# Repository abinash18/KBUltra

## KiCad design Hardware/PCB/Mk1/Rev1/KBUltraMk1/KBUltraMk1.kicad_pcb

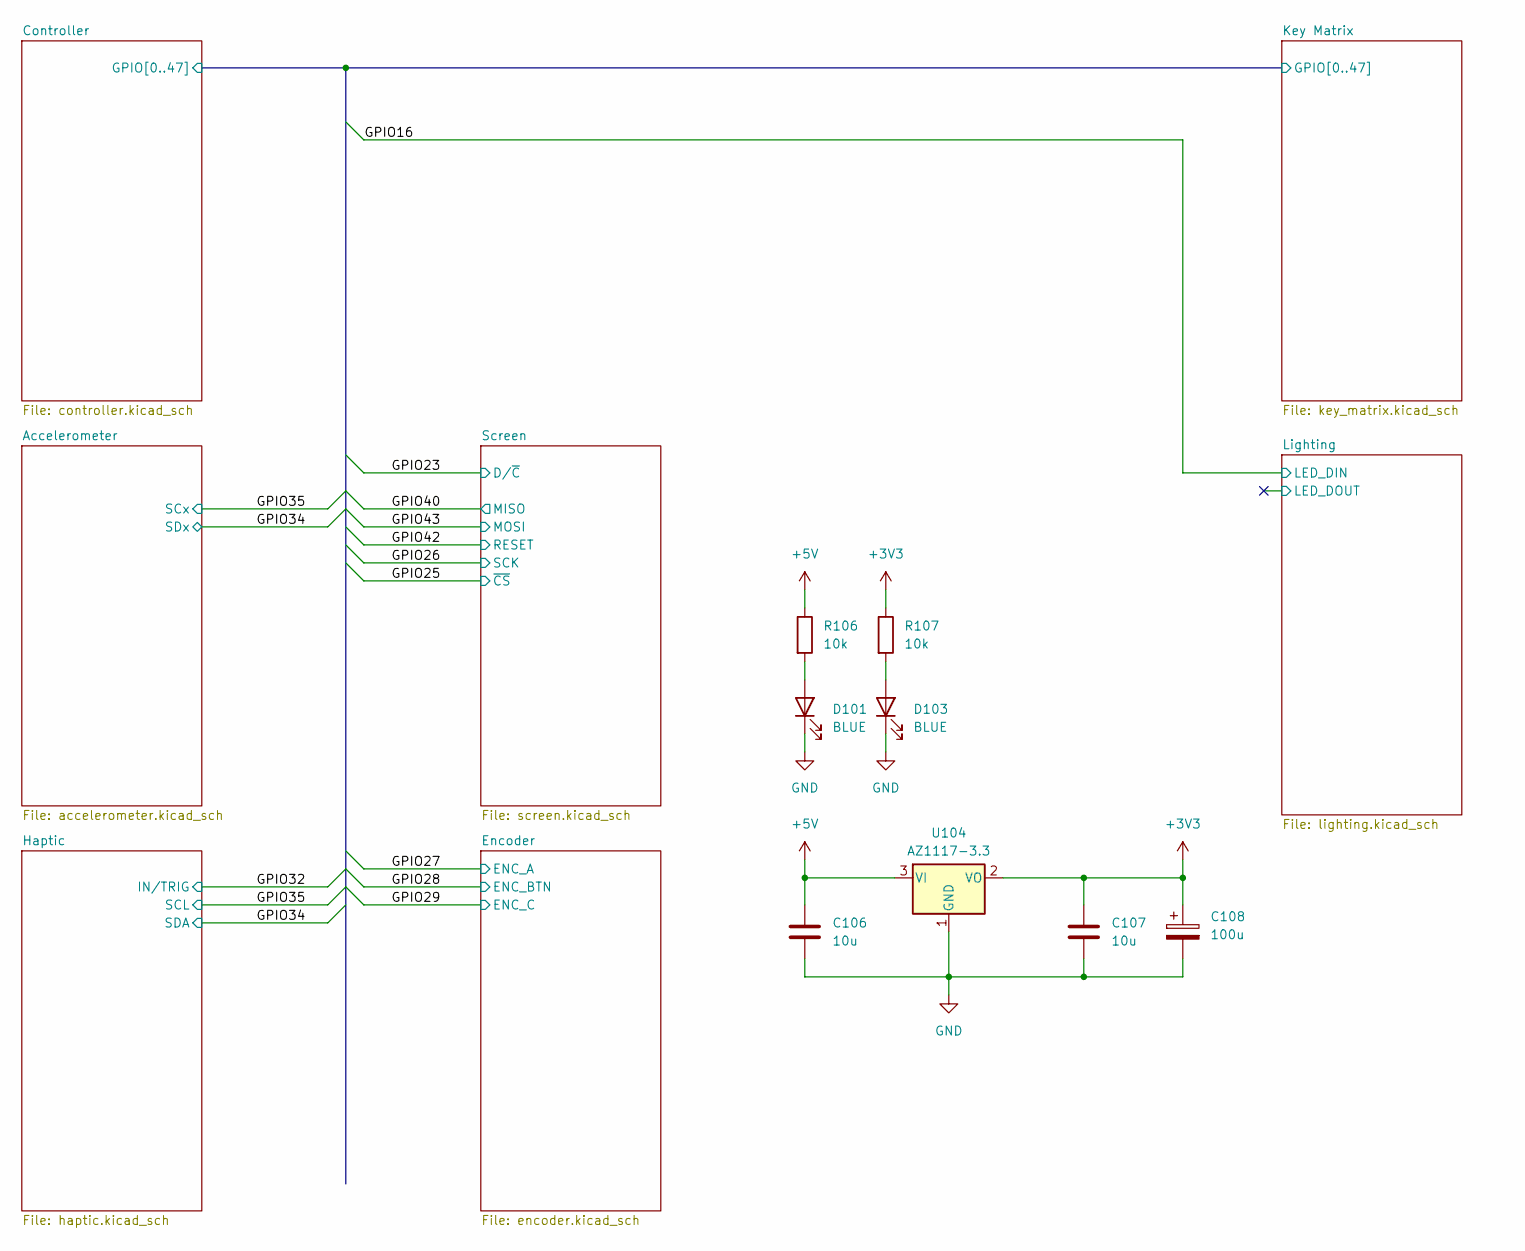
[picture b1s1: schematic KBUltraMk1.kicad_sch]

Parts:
C106, C107: 10u; C_0603_1608Metric; JLC Part# C96446
C108: 100u; CP_EIA-3528-21_Kemet-B_HandSolder; JLC Part# C16133
D101, D103: BLUE; LED_0603_1608Metric
R106, R107: 10k; R_0603_1608Metric; JLC Part# C25804
U104: AZ1117-3.3; SOT-223-3_TabPin2

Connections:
+3V3: C107.2, C108.1, R107.1, U104.2 (VO); also elsewhere on the board
+5V: C106.2, R106.1, U104.3 (VI); also elsewhere on the board
GND: C106.1, C107.1, C108.2, D101.1 (K), D103.1 (K), U104.1 (GND); also elsewhere on the board
unnamed: D101.2 (A), R106.2
unnamed: D103.2 (A), R107.2

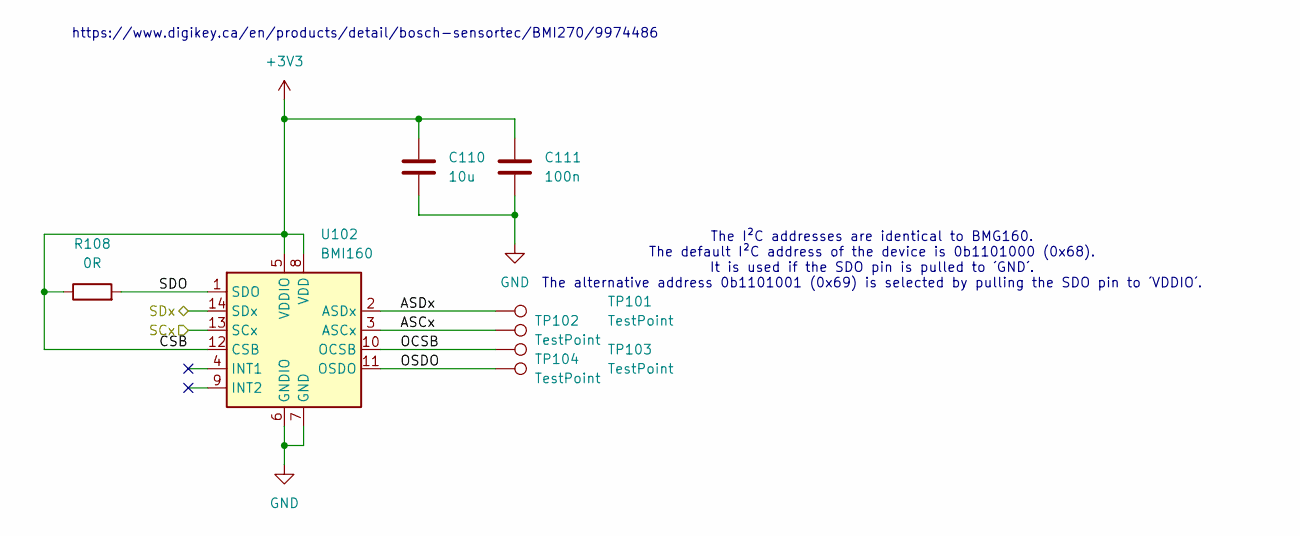
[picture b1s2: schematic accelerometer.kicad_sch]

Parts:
C110: 10u; C_0603_1608Metric; JLC Part# C96446
C111: 100n; C_0603_1608Metric; JLC Part# C14663
R108: 0R; R_0603_1608Metric; JLC Part# C21189
TP101, TP102, TP103, TP104: TestPoint; TestPoint_Pad_D1.0mm
U102: BMI160; Bosch_LGA-14_3x2.5mm_P0.5mm

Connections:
+3V3: C110.1, C111.1, R108.1, U102.5 (VDDIO), U102.8 (VDD), U102.12 (CSB); also elsewhere on the board
/Accelerometer/ASCx: TP102.1 (1_1), U102.3 (ASCx)
/Accelerometer/ASDx: TP101.1 (1_1), U102.2 (ASDx)
/Accelerometer/OCSB: TP103.1 (1_1), U102.10 (OCSB)
/Accelerometer/OSDO: TP104.1 (1_1), U102.11 (OSDO)
/Accelerometer/SDO: R108.2, U102.1 (SDO)
/Controller/GPIO34: U102.14 (SDx); also elsewhere on the board
/Controller/GPIO35: U102.13 (SCx); also elsewhere on the board
GND: C110.2, C111.2, U102.6 (GNDIO), U102.7 (GND); also elsewhere on the board

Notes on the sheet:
The I²C addresses are identical to BMG160. The default I²C address of the device is 0b1101000 (0x68). It is used if the SDO pin is pulled to ´GND´. The alternative address 0b1101001 (0x69) is selected by pulling the SDO pin to ´VDDIO´.
https://www.digikey.ca/en/products/detail/bosch-sensortec/BMI270/9974486

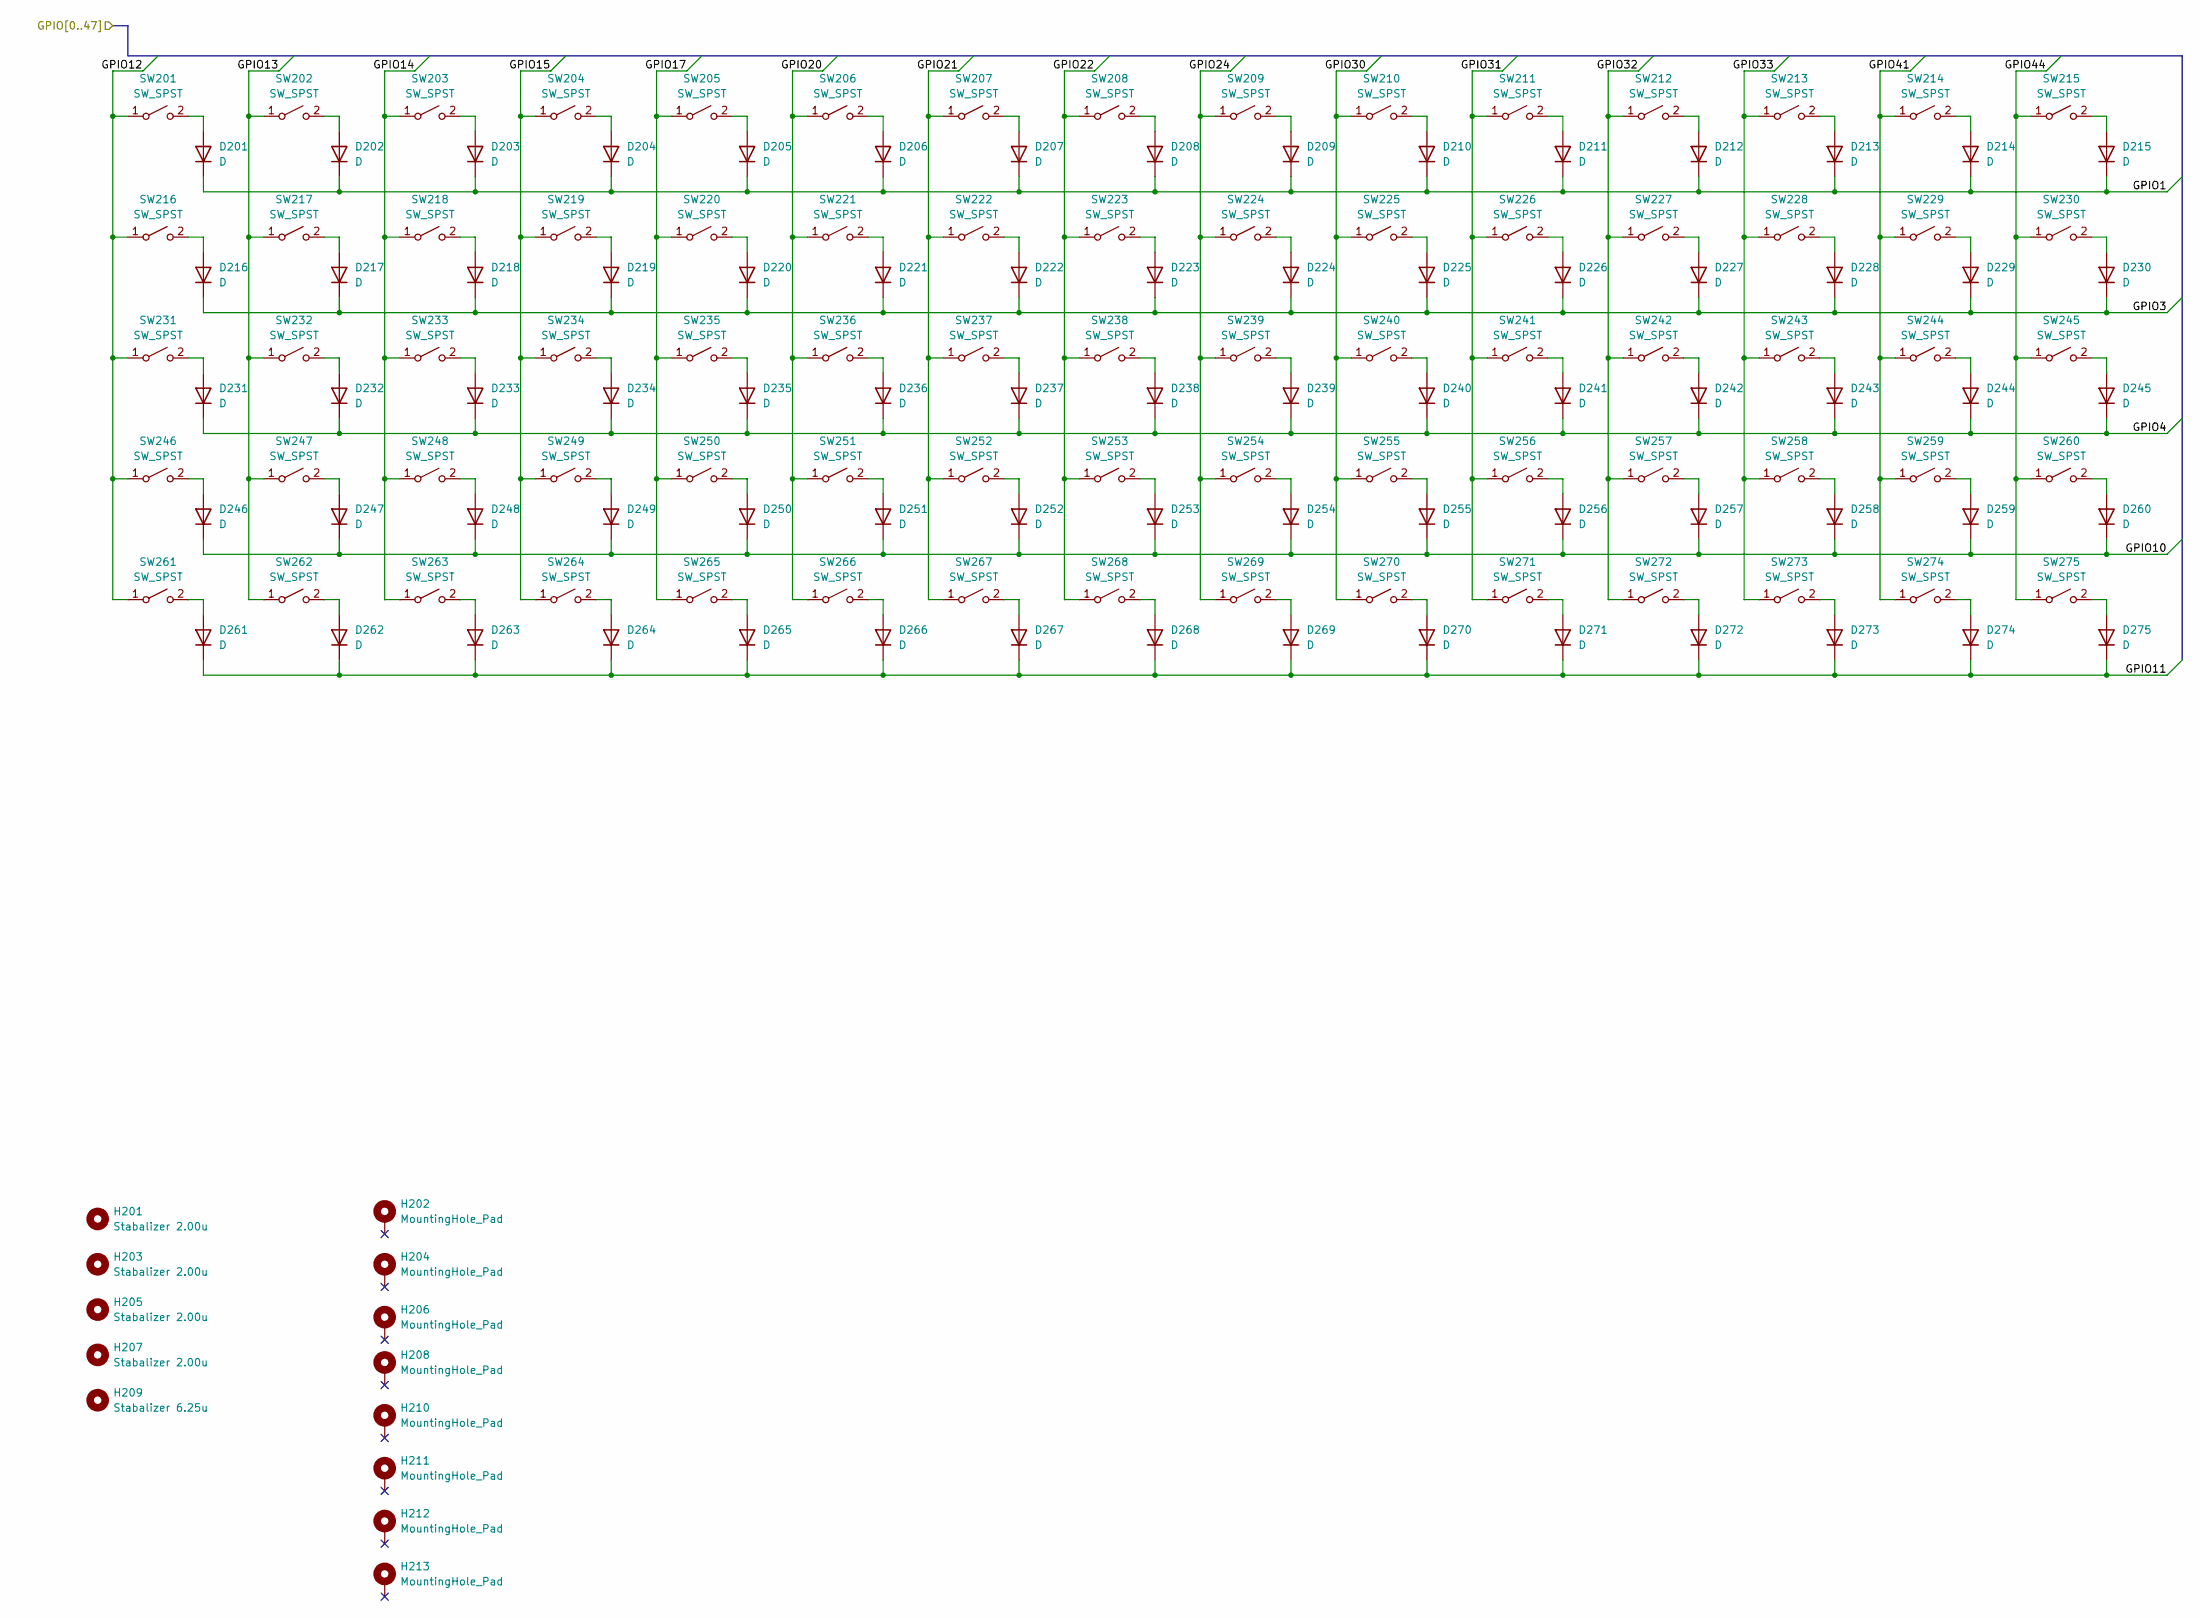
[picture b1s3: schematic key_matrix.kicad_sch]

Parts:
D201, D202, D203, D204, D205, D206, D207, D208, D209, D210, D211, D212, D213, D214, D215, D216, D217, D218, D219, D220, D221, D222, D223, D224, D225, D226, D227, D228, D229, D230, D231, D232, D233, D234, D235, D236, D237, D238, D239, D240, D241, D242, D243, D244, D245, D246, D247, D248, D249, D250, D251, D252, D253, D254, D255, D256, D257, D258, D259, D260, D261, D262, D263, D264, D265, D266, D267, D268, D269, D270, D271, D272, D273, D274, D275: D; D_SOD-123; JLC Part# C81598
H201, H203, H205, H207: Stabalizer 2.00u; Stabilizer_Cherry_MX_2.00u
H202, H204, H206, H208, H210, H211, H212, H213: MountingHole_Pad; MountingHole_3.2mm_M3_Pad_Via
H209: Stabalizer 6.25u; Stabilizer_Cherry_MX_6.25u
SW201, SW202, SW203, SW204, SW205, SW206, SW207, SW208, SW209, SW210, SW211, SW212, SW213, SW214, SW215, SW216, SW217, SW218, SW219, SW220, SW221, SW222, SW223, SW224, SW226, SW228, SW229, SW230, SW231, SW232, SW233, SW234, SW235, SW236, SW237, SW238, SW239, SW241, SW243, SW244, SW245, SW246, SW247, SW248, SW249, SW250, SW251, SW252, SW253, SW255, SW257, SW258, SW259, SW260, SW261, SW262, SW263, SW264, SW265, SW266: SW_SPST; SW_Hotswap_Kailh_MX_Plated_1.00u; JLC Part# C41430893
SW225: SW_SPST; SW_Hotswap_Kailh_MX_Plated_2.00u; JLC Part# C41430893
SW227, SW240: SW_SPST; SW_Hotswap_Kailh_MX_Plated_1.50u; JLC Part# C41430893
SW242: SW_SPST; SW_Hotswap_Kailh_MX_Plated_1.75u; JLC Part# C41430893
SW254, SW256: SW_SPST; SW_Hotswap_Kailh_MX_Plated_2.25u; JLC Part# C41430893
SW267: SW_SPST; SW_Hotswap_Kailh_MX_Plated_2.75u; JLC Part# C41430893
SW268, SW269, SW270, SW272, SW273, SW274, SW275: SW_SPST; SW_Hotswap_Kailh_MX_Plated_1.25u; JLC Part# C41430893
SW271: SW_SPST; SW_Hotswap_Kailh_MX_Plated_6.25u; JLC Part# C41430893

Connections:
/Controller/GPIO1: D201.1 (K), D202.1 (K), D203.1 (K), D204.1 (K), D205.1 (K), D206.1 (K), D207.1 (K), D208.1 (K), D209.1 (K), D210.1 (K), D211.1 (K), D212.1 (K), D213.1 (K), D214.1 (K), D215.1 (K); also elsewhere on the board
/Controller/GPIO3: D216.1 (K), D217.1 (K), D218.1 (K), D219.1 (K), D220.1 (K), D221.1 (K), D222.1 (K), D223.1 (K), D224.1 (K), D225.1 (K), D226.1 (K), D227.1 (K), D228.1 (K), D229.1 (K), D230.1 (K); also elsewhere on the board
/Controller/GPIO4: D231.1 (K), D232.1 (K), D233.1 (K), D234.1 (K), D235.1 (K), D236.1 (K), D237.1 (K), D238.1 (K), D239.1 (K), D240.1 (K), D241.1 (K), D242.1 (K), D243.1 (K), D244.1 (K), D245.1 (K); also elsewhere on the board
/Controller/GPIO10: D246.1 (K), D247.1 (K), D248.1 (K), D249.1 (K), D250.1 (K), D251.1 (K), D252.1 (K), D253.1 (K), D254.1 (K), D255.1 (K), D256.1 (K), D257.1 (K), D258.1 (K), D259.1 (K), D260.1 (K); also elsewhere on the board
/Controller/GPIO11: D261.1 (K), D262.1 (K), D263.1 (K), D264.1 (K), D265.1 (K), D266.1 (K), D267.1 (K), D268.1 (K), D269.1 (K), D270.1 (K), D271.1 (K), D272.1 (K), D273.1 (K), D274.1 (K), D275.1 (K); also elsewhere on the board
/Controller/GPIO12: SW201.1 (A), SW216.1 (A), SW231.1 (A), SW246.1 (A), SW261.1 (A); also elsewhere on the board
/Controller/GPIO13: SW202.1 (A), SW217.1 (A), SW232.1 (A), SW247.1 (A), SW262.1 (A); also elsewhere on the board
/Controller/GPIO14: SW203.1 (A), SW218.1 (A), SW233.1 (A), SW248.1 (A), SW263.1 (A); also elsewhere on the board
/Controller/GPIO15: SW204.1 (A), SW219.1 (A), SW234.1 (A), SW249.1 (A), SW264.1 (A); also elsewhere on the board
/Controller/GPIO17: SW205.1 (A), SW220.1 (A), SW235.1 (A), SW250.1 (A), SW265.1 (A); also elsewhere on the board
/Controller/GPIO20: SW206.1 (A), SW221.1 (A), SW236.1 (A), SW251.1 (A), SW266.1 (A); also elsewhere on the board
/Controller/GPIO21: SW207.1 (A), SW222.1 (A), SW237.1 (A), SW252.1 (A), SW267.1 (A); also elsewhere on the board
/Controller/GPIO22: SW208.1 (A), SW223.1 (A), SW238.1 (A), SW253.1 (A), SW268.1 (A); also elsewhere on the board
/Controller/GPIO24: SW209.1 (A), SW224.1 (A), SW239.1 (A), SW254.1 (A), SW269.1 (A); also elsewhere on the board
/Controller/GPIO30: SW210.1 (A), SW225.1 (A), SW240.1 (A), SW255.1 (A), SW270.1 (A); also elsewhere on the board
/Controller/GPIO31: SW211.1 (A), SW226.1 (A), SW241.1 (A), SW256.1 (A), SW271.1 (A); also elsewhere on the board
/Controller/GPIO32: SW212.1 (A), SW227.1 (A), SW242.1 (A), SW257.1 (A), SW272.1 (A); also elsewhere on the board
/Controller/GPIO33: SW213.1 (A), SW228.1 (A), SW243.1 (A), SW258.1 (A), SW273.1 (A); also elsewhere on the board
/Controller/GPIO41: SW214.1 (A), SW229.1 (A), SW244.1 (A), SW259.1 (A), SW274.1 (A); also elsewhere on the board
/Controller/GPIO44: SW215.1 (A), SW230.1 (A), SW245.1 (A), SW260.1 (A), SW275.1 (A); also elsewhere on the board
unnamed: D201.2 (A), SW201.2 (B)
unnamed: D202.2 (A), SW202.2 (B)
unnamed: D203.2 (A), SW203.2 (B)
unnamed: D204.2 (A), SW204.2 (B)
unnamed: D205.2 (A), SW205.2 (B)
unnamed: D206.2 (A), SW206.2 (B)
unnamed: D207.2 (A), SW207.2 (B)
unnamed: D208.2 (A), SW208.2 (B)
unnamed: D209.2 (A), SW209.2 (B)
unnamed: D210.2 (A), SW210.2 (B)
unnamed: D211.2 (A), SW211.2 (B)
unnamed: D212.2 (A), SW212.2 (B)
unnamed: D213.2 (A), SW213.2 (B)
unnamed: D214.2 (A), SW214.2 (B)
unnamed: D215.2 (A), SW215.2 (B)
unnamed: D216.2 (A), SW216.2 (B)
unnamed: D217.2 (A), SW217.2 (B)
unnamed: D218.2 (A), SW218.2 (B)
unnamed: D219.2 (A), SW219.2 (B)
unnamed: D220.2 (A), SW220.2 (B)
unnamed: D221.2 (A), SW221.2 (B)
unnamed: D222.2 (A), SW222.2 (B)
unnamed: D223.2 (A), SW223.2 (B)
unnamed: D224.2 (A), SW224.2 (B)
unnamed: D225.2 (A), SW225.2 (B)
unnamed: D226.2 (A), SW226.2 (B)
unnamed: D227.2 (A), SW227.2 (B)
unnamed: D228.2 (A), SW228.2 (B)
unnamed: D229.2 (A), SW229.2 (B)
unnamed: D230.2 (A), SW230.2 (B)
unnamed: D231.2 (A), SW231.2 (B)
unnamed: D232.2 (A), SW232.2 (B)
unnamed: D233.2 (A), SW233.2 (B)
unnamed: D234.2 (A), SW234.2 (B)
unnamed: D235.2 (A), SW235.2 (B)
unnamed: D236.2 (A), SW236.2 (B)
unnamed: D237.2 (A), SW237.2 (B)
unnamed: D238.2 (A), SW238.2 (B)
unnamed: D239.2 (A), SW239.2 (B)
unnamed: D240.2 (A), SW240.2 (B)
unnamed: D241.2 (A), SW241.2 (B)
unnamed: D242.2 (A), SW242.2 (B)
unnamed: D243.2 (A), SW243.2 (B)
unnamed: D244.2 (A), SW244.2 (B)
unnamed: D245.2 (A), SW245.2 (B)
unnamed: D246.2 (A), SW246.2 (B)
unnamed: D247.2 (A), SW247.2 (B)
unnamed: D248.2 (A), SW248.2 (B)
unnamed: D249.2 (A), SW249.2 (B)
unnamed: D250.2 (A), SW250.2 (B)
unnamed: D251.2 (A), SW251.2 (B)
unnamed: D252.2 (A), SW252.2 (B)
unnamed: D253.2 (A), SW253.2 (B)
unnamed: D254.2 (A), SW254.2 (B)
unnamed: D255.2 (A), SW255.2 (B)
unnamed: D256.2 (A), SW256.2 (B)
unnamed: D257.2 (A), SW257.2 (B)
unnamed: D258.2 (A), SW258.2 (B)
unnamed: D259.2 (A), SW259.2 (B)
unnamed: D260.2 (A), SW260.2 (B)
unnamed: D261.2 (A), SW261.2 (B)
unnamed: D262.2 (A), SW262.2 (B)
unnamed: D263.2 (A), SW263.2 (B)
unnamed: D264.2 (A), SW264.2 (B)
unnamed: D265.2 (A), SW265.2 (B)
unnamed: D266.2 (A), SW266.2 (B)
unnamed: D267.2 (A), SW267.2 (B)
unnamed: D268.2 (A), SW268.2 (B)
unnamed: D269.2 (A), SW269.2 (B)
unnamed: D270.2 (A), SW270.2 (B)
unnamed: D271.2 (A), SW271.2 (B)
unnamed: D272.2 (A), SW272.2 (B)
unnamed: D273.2 (A), SW273.2 (B)
unnamed: D274.2 (A), SW274.2 (B)
unnamed: D275.2 (A), SW275.2 (B)

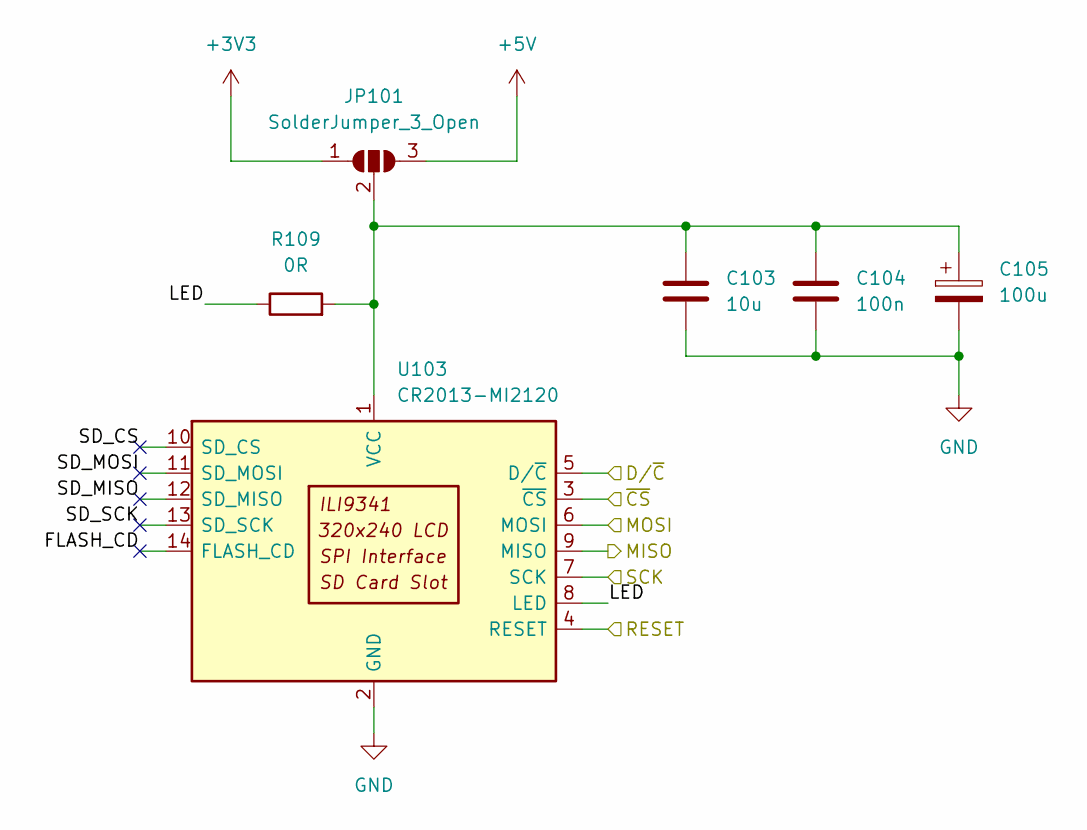
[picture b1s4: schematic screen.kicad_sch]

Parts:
C103: 10u; C_0603_1608Metric; JLC Part# C96446
C104: 100n; C_0603_1608Metric; JLC Part# C14663
C105: 100u; CP_EIA-3528-21_Kemet-B_HandSolder; JLC Part# C16133
JP101: SolderJumper_3_Open; SolderJumper-3_P2.0mm_Open_TrianglePad1.0x1.5mm_NumberLabels
R109: 0R; R_0603_1608Metric; JLC Part# C21189
U103: CR2013-MI2120

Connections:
+3V3: JP101.1 (A); also elsewhere on the board
+5V: JP101.3 (B); also elsewhere on the board
/Controller/GPIO23: U103.5 (D/~C); also elsewhere on the board
/Controller/GPIO25: U103.3 (~CS); also elsewhere on the board
/Controller/GPIO26: U103.7 (SCK); also elsewhere on the board
/Controller/GPIO40: U103.9 (MISO); also elsewhere on the board
/Controller/GPIO42: U103.4 (RESET); also elsewhere on the board
/Controller/GPIO43: U103.6 (MOSI); also elsewhere on the board
/Screen/LED: R109.1, U103.8 (LED)
GND: C103.2, C104.2, C105.2, U103.2 (GND); also elsewhere on the board
unnamed: C103.1, C104.1, C105.1, JP101.2 (C), R109.2, U103.1 (VCC)

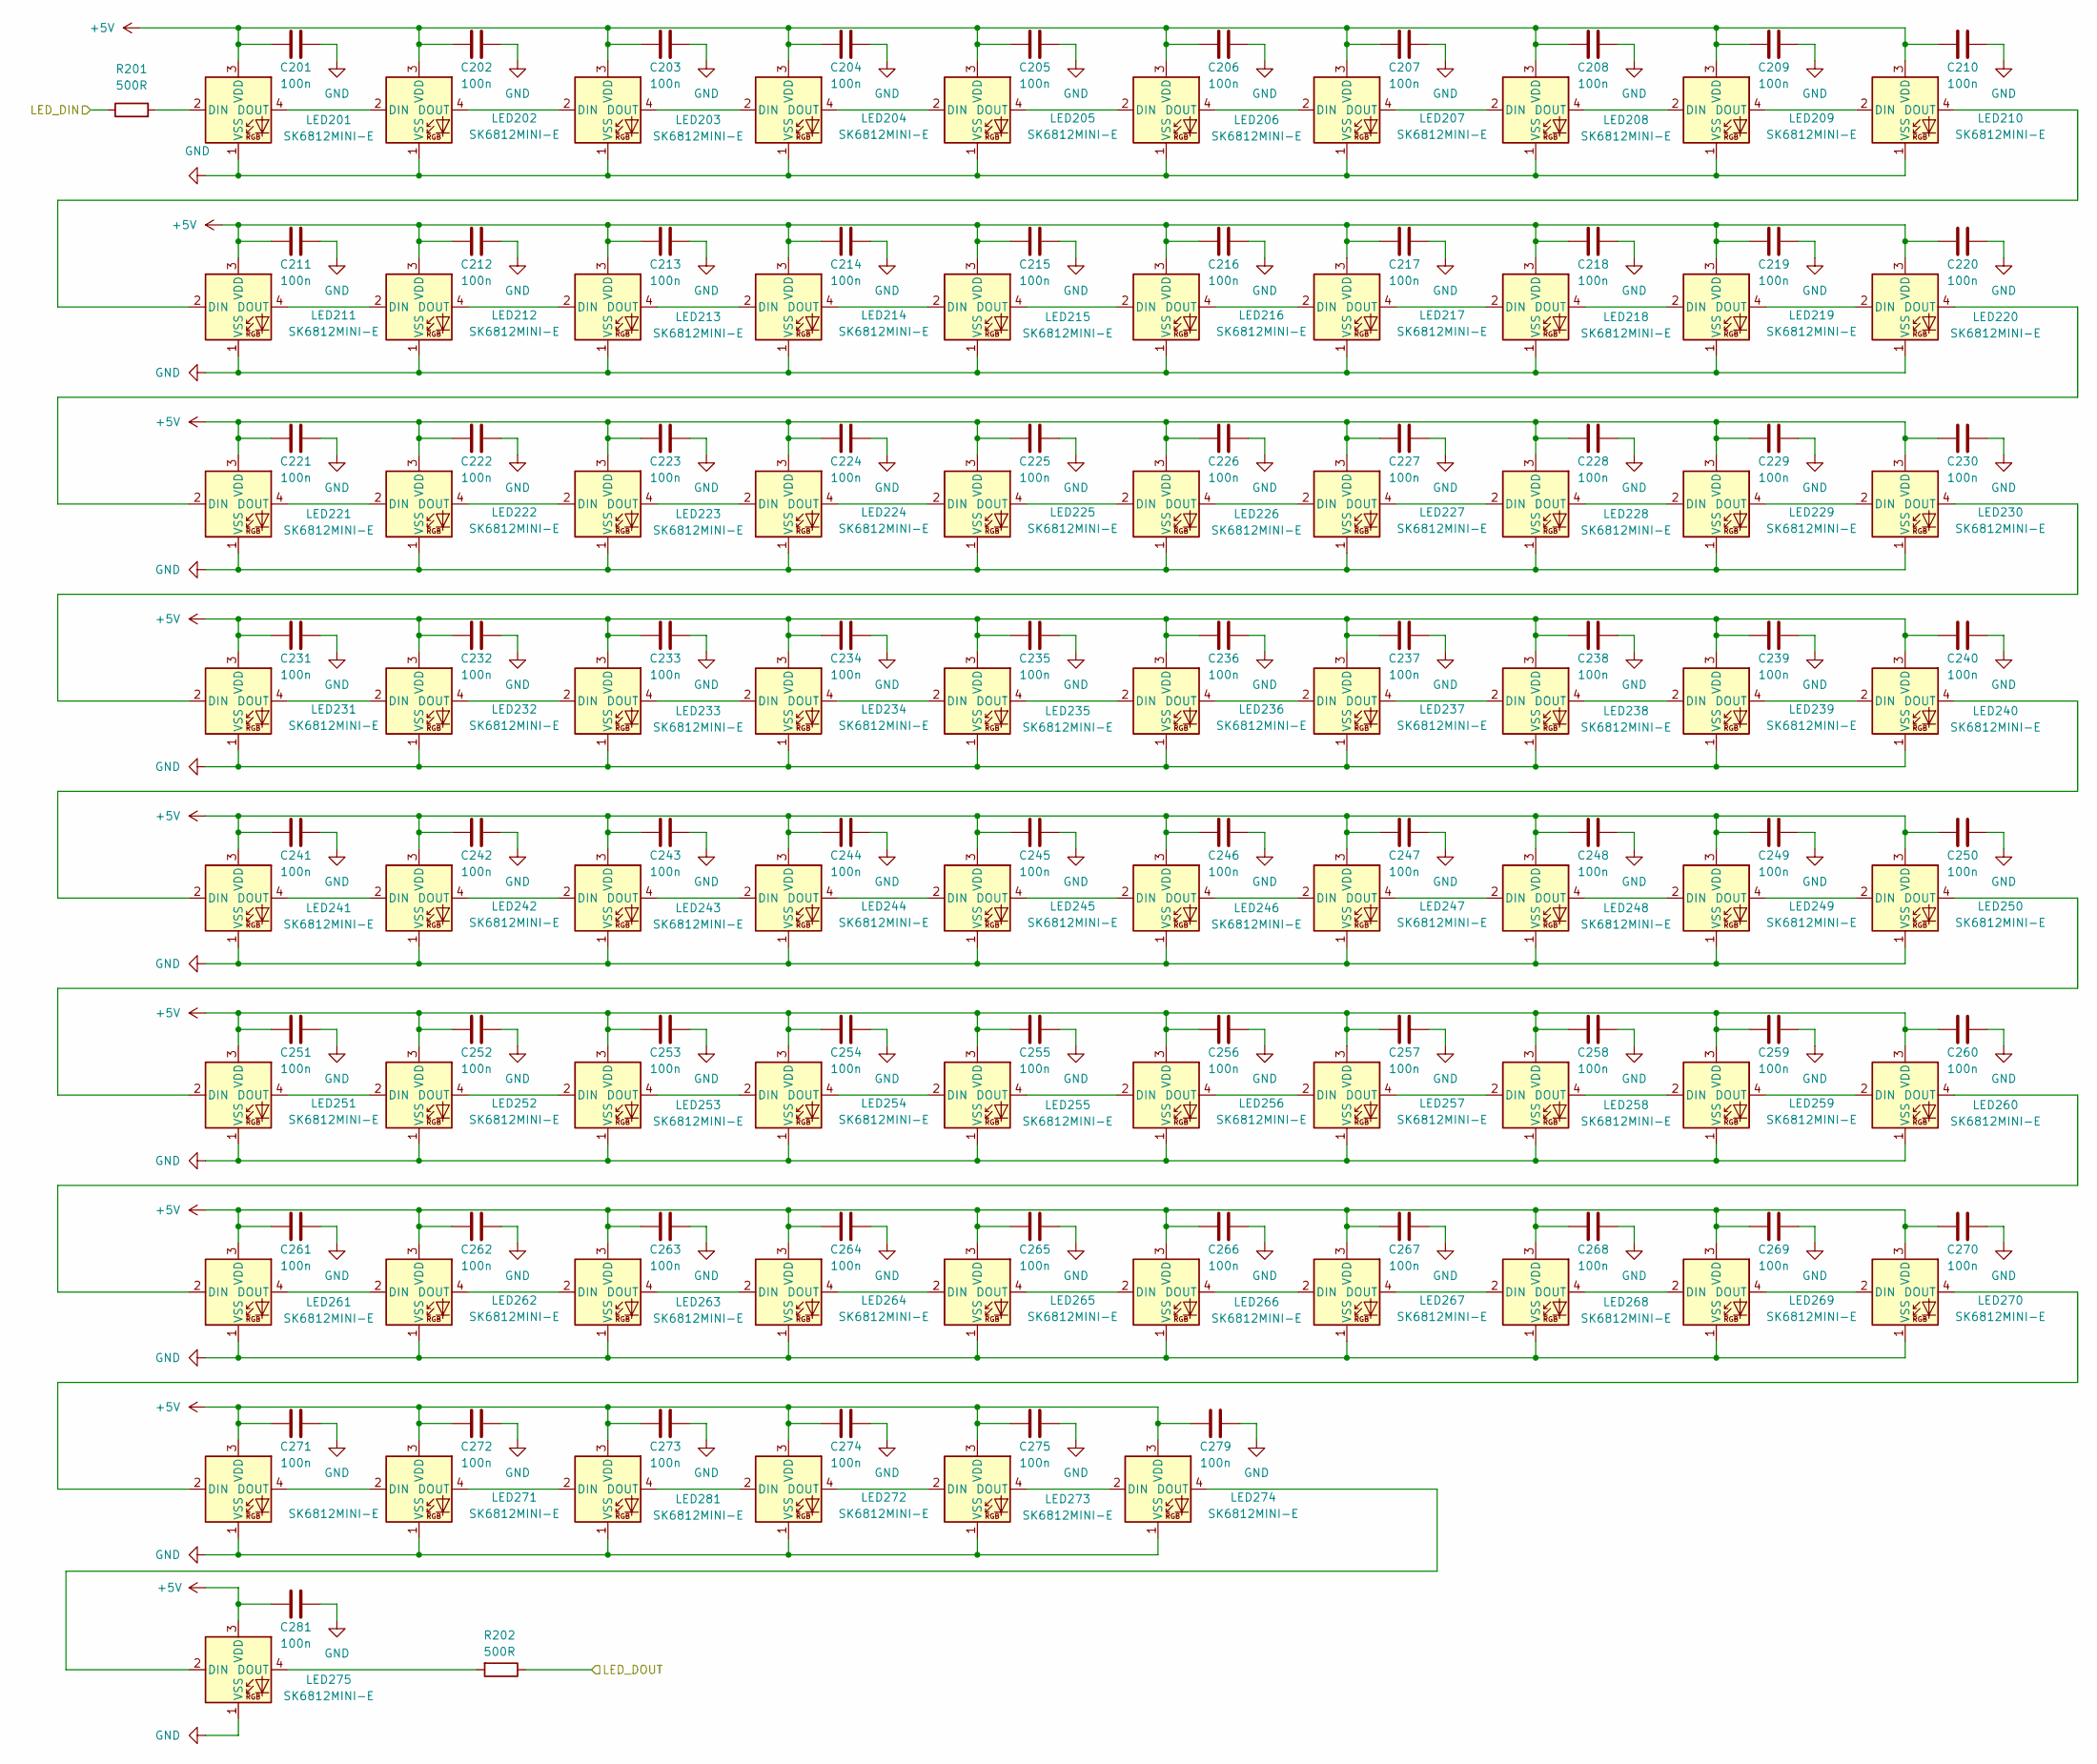
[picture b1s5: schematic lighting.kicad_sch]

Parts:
C201, C202, C203, C204, C205, C206, C207, C208, C209, C210, C211, C212, C213, C214, C215, C216, C217, C218, C219, C220, C221, C222, C223, C224, C225, C226, C227, C228, C229, C230, C231, C232, C233, C234, C235, C236, C237, C238, C239, C240, C241, C242, C243, C244, C245, C246, C247, C248, C249, C250, C251, C252, C253, C254, C255, C256, C257, C258, C259, C260, C261, C262, C263, C264, C265, C266, C267, C268, C269, C270, C271, C272, C273, C274, C275, C279, C281: 100n; C_0603_1608Metric; JLC Part# C14663
LED201, LED202, LED203, LED204, LED205, LED206, LED207, LED208, LED209, LED210, LED211, LED212, LED213, LED214, LED215, LED216, LED217, LED218, LED219, LED220, LED221, LED222, LED223, LED224, LED225, LED226, LED227, LED228, LED229, LED230, LED231, LED232, LED233, LED234, LED235, LED236, LED237, LED238, LED239, LED240, LED241, LED242, LED243, LED244, LED245, LED246, LED247, LED248, LED249, LED250, LED251, LED252, LED253, LED254, LED255, LED256, LED257, LED258, LED259, LED260, LED261, LED262, LED263, LED264, LED265, LED266, LED267, LED268, LED269, LED270, LED271, LED272, LED273, LED274, LED275, LED279, LED281: SK6812MINI-E; LED_SK6812MINI-E_3.2x2.8mm_P1.5mm_ReverseMount
R201, R202: 500R; R_0603_1608Metric; JLC Part# C23193

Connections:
+5V: C201.1, C202.1, C203.1, C204.1, C205.1, C206.1, C207.1, C208.1, C209.1, C210.1, C211.1, C212.1, C213.1, C214.1, C215.1, C216.1, C217.1, C218.1, C219.1, C220.1, C221.1, C222.1, C223.1, C224.1, C225.1, C226.1, C227.1, C228.1, C229.1, C230.1, C231.1, C232.1, C233.1, C234.1, C235.1, C236.1, C237.1, C238.1, C239.1, C240.1, C241.1, C242.1, C243.1, C244.1, C245.1, C246.1, C247.1, C248.1, C249.1, C250.1, C251.1, C252.1, C253.1, C254.1, C255.1, C256.1, C257.1, C258.1, C259.1, C260.1, C261.1, C262.1, C263.1, C264.1, C265.1, C266.1, C267.1, C268.1, C269.1, C270.1, C271.1, C272.1, C273.1, C274.1, C275.1, C279.1, C281.1, LED201.3 (VDD), LED202.3 (VDD), LED203.3 (VDD), LED204.3 (VDD), LED205.3 (VDD), LED206.3 (VDD), LED207.3 (VDD), LED208.3 (VDD), LED209.3 (VDD), LED210.3 (VDD), LED211.3 (VDD), LED212.3 (VDD), LED213.3 (VDD), LED214.3 (VDD), LED215.3 (VDD), LED216.3 (VDD), LED217.3 (VDD), LED218.3 (VDD), LED219.3 (VDD), LED220.3 (VDD), LED221.3 (VDD), LED222.3 (VDD), LED223.3 (VDD), LED224.3 (VDD), LED225.3 (VDD), LED226.3 (VDD), LED227.3 (VDD), LED228.3 (VDD), LED229.3 (VDD), LED230.3 (VDD), LED231.3 (VDD), LED232.3 (VDD), LED233.3 (VDD), LED234.3 (VDD), LED235.3 (VDD), LED236.3 (VDD), LED237.3 (VDD), LED238.3 (VDD), LED239.3 (VDD), LED240.3 (VDD), LED241.3 (VDD), LED242.3 (VDD), LED243.3 (VDD), LED244.3 (VDD), LED245.3 (VDD), LED246.3 (VDD), LED247.3 (VDD), LED248.3 (VDD), LED249.3 (VDD), LED250.3 (VDD), LED251.3 (VDD), LED252.3 (VDD), LED253.3 (VDD), LED254.3 (VDD), LED255.3 (VDD), LED256.3 (VDD), LED257.3 (VDD), LED258.3 (VDD), LED259.3 (VDD), LED260.3 (VDD), LED261.3 (VDD), LED262.3 (VDD), LED263.3 (VDD), LED264.3 (VDD), LED265.3 (VDD), LED266.3 (VDD), LED267.3 (VDD), LED268.3 (VDD), LED269.3 (VDD), LED270.3 (VDD), LED271.3 (VDD), LED272.3 (VDD), LED273.3 (VDD), LED274.3 (VDD), LED275.3 (VDD), LED279.3 (VDD), LED281.3 (VDD); also elsewhere on the board
/Controller/GPIO16: R201.1; also elsewhere on the board
/Lighting/LED_DOUT: R202.1
GND: C201.2, C202.2, C203.2, C204.2, C205.2, C206.2, C207.2, C208.2, C209.2, C210.2, C211.2, C212.2, C213.2, C214.2, C215.2, C216.2, C217.2, C218.2, C219.2, C220.2, C221.2, C222.2, C223.2, C224.2, C225.2, C226.2, C227.2, C228.2, C229.2, C230.2, C231.2, C232.2, C233.2, C234.2, C235.2, C236.2, C237.2, C238.2, C239.2, C240.2, C241.2, C242.2, C243.2, C244.2, C245.2, C246.2, C247.2, C248.2, C249.2, C250.2, C251.2, C252.2, C253.2, C254.2, C255.2, C256.2, C257.2, C258.2, C259.2, C260.2, C261.2, C262.2, C263.2, C264.2, C265.2, C266.2, C267.2, C268.2, C269.2, C270.2, C271.2, C272.2, C273.2, C274.2, C275.2, C279.2, C281.2, LED201.1 (VSS), LED202.1 (VSS), LED203.1 (VSS), LED204.1 (VSS), LED205.1 (VSS), LED206.1 (VSS), LED207.1 (VSS), LED208.1 (VSS), LED209.1 (VSS), LED210.1 (VSS), LED211.1 (VSS), LED212.1 (VSS), LED213.1 (VSS), LED214.1 (VSS), LED215.1 (VSS), LED216.1 (VSS), LED217.1 (VSS), LED218.1 (VSS), LED219.1 (VSS), LED220.1 (VSS), LED221.1 (VSS), LED222.1 (VSS), LED223.1 (VSS), LED224.1 (VSS), LED225.1 (VSS), LED226.1 (VSS), LED227.1 (VSS), LED228.1 (VSS), LED229.1 (VSS), LED230.1 (VSS), LED231.1 (VSS), LED232.1 (VSS), LED233.1 (VSS), LED234.1 (VSS), LED235.1 (VSS), LED236.1 (VSS), LED237.1 (VSS), LED238.1 (VSS), LED239.1 (VSS), LED240.1 (VSS), LED241.1 (VSS), LED242.1 (VSS), LED243.1 (VSS), LED244.1 (VSS), LED245.1 (VSS), LED246.1 (VSS), LED247.1 (VSS), LED248.1 (VSS), LED249.1 (VSS), LED250.1 (VSS), LED251.1 (VSS), LED252.1 (VSS), LED253.1 (VSS), LED254.1 (VSS), LED255.1 (VSS), LED256.1 (VSS), LED257.1 (VSS), LED258.1 (VSS), LED259.1 (VSS), LED260.1 (VSS), LED261.1 (VSS), LED262.1 (VSS), LED263.1 (VSS), LED264.1 (VSS), LED265.1 (VSS), LED266.1 (VSS), LED267.1 (VSS), LED268.1 (VSS), LED269.1 (VSS), LED270.1 (VSS), LED271.1 (VSS), LED272.1 (VSS), LED273.1 (VSS), LED274.1 (VSS), LED275.1 (VSS), LED279.1 (VSS), LED281.1 (VSS); also elsewhere on the board
unnamed: LED201.2 (DIN), R201.2
unnamed: LED201.4 (DOUT), LED202.2 (DIN)
unnamed: LED202.4 (DOUT), LED203.2 (DIN)
unnamed: LED203.4 (DOUT), LED204.2 (DIN)
unnamed: LED204.4 (DOUT), LED205.2 (DIN)
unnamed: LED205.4 (DOUT), LED206.2 (DIN)
unnamed: LED206.4 (DOUT), LED207.2 (DIN)
unnamed: LED207.4 (DOUT), LED208.2 (DIN)
unnamed: LED208.4 (DOUT), LED209.2 (DIN)
unnamed: LED209.4 (DOUT), LED210.2 (DIN)
unnamed: LED210.4 (DOUT), LED211.2 (DIN)
unnamed: LED211.4 (DOUT), LED212.2 (DIN)
unnamed: LED212.4 (DOUT), LED213.2 (DIN)
unnamed: LED213.4 (DOUT), LED214.2 (DIN)
unnamed: LED214.4 (DOUT), LED215.2 (DIN)
unnamed: LED215.4 (DOUT), LED216.2 (DIN)
unnamed: LED216.4 (DOUT), LED217.2 (DIN)
unnamed: LED217.4 (DOUT), LED218.2 (DIN)
unnamed: LED218.4 (DOUT), LED219.2 (DIN)
unnamed: LED219.4 (DOUT), LED220.2 (DIN)
unnamed: LED220.4 (DOUT), LED221.2 (DIN)
unnamed: LED221.4 (DOUT), LED222.2 (DIN)
unnamed: LED222.4 (DOUT), LED223.2 (DIN)
unnamed: LED223.4 (DOUT), LED224.2 (DIN)
unnamed: LED224.4 (DOUT), LED225.2 (DIN)
unnamed: LED225.4 (DOUT), LED226.2 (DIN)
unnamed: LED226.4 (DOUT), LED227.2 (DIN)
unnamed: LED227.4 (DOUT), LED228.2 (DIN)
unnamed: LED228.4 (DOUT), LED229.2 (DIN)
unnamed: LED229.4 (DOUT), LED230.2 (DIN)
unnamed: LED230.4 (DOUT), LED231.2 (DIN)
unnamed: LED231.4 (DOUT), LED232.2 (DIN)
unnamed: LED232.4 (DOUT), LED233.2 (DIN)
unnamed: LED233.4 (DOUT), LED234.2 (DIN)
unnamed: LED234.4 (DOUT), LED235.2 (DIN)
unnamed: LED235.4 (DOUT), LED236.2 (DIN)
unnamed: LED236.4 (DOUT), LED237.2 (DIN)
unnamed: LED237.4 (DOUT), LED238.2 (DIN)
unnamed: LED238.4 (DOUT), LED239.2 (DIN)
unnamed: LED239.4 (DOUT), LED240.2 (DIN)
unnamed: LED240.4 (DOUT), LED241.2 (DIN)
unnamed: LED241.4 (DOUT), LED242.2 (DIN)
unnamed: LED242.4 (DOUT), LED243.2 (DIN)
unnamed: LED243.4 (DOUT), LED244.2 (DIN)
unnamed: LED244.4 (DOUT), LED245.2 (DIN)
unnamed: LED245.4 (DOUT), LED246.2 (DIN)
unnamed: LED246.4 (DOUT), LED247.2 (DIN)
unnamed: LED247.4 (DOUT), LED248.2 (DIN)
unnamed: LED248.4 (DOUT), LED249.2 (DIN)
unnamed: LED249.4 (DOUT), LED250.2 (DIN)
unnamed: LED250.4 (DOUT), LED251.2 (DIN)
unnamed: LED251.4 (DOUT), LED252.2 (DIN)
unnamed: LED252.4 (DOUT), LED253.2 (DIN)
unnamed: LED253.4 (DOUT), LED254.2 (DIN)
unnamed: LED254.4 (DOUT), LED255.2 (DIN)
unnamed: LED255.4 (DOUT), LED256.2 (DIN)
unnamed: LED256.4 (DOUT), LED257.2 (DIN)
unnamed: LED257.4 (DOUT), LED258.2 (DIN)
unnamed: LED258.4 (DOUT), LED259.2 (DIN)
unnamed: LED259.4 (DOUT), LED260.2 (DIN)
unnamed: LED260.4 (DOUT), LED261.2 (DIN)
unnamed: LED261.4 (DOUT), LED262.2 (DIN)
unnamed: LED262.4 (DOUT), LED263.2 (DIN)
unnamed: LED263.4 (DOUT), LED264.2 (DIN)
unnamed: LED264.4 (DOUT), LED265.2 (DIN)
unnamed: LED265.4 (DOUT), LED266.2 (DIN)
unnamed: LED266.4 (DOUT), LED267.2 (DIN)
unnamed: LED267.4 (DOUT), LED268.2 (DIN)
unnamed: LED268.4 (DOUT), LED269.2 (DIN)
unnamed: LED269.4 (DOUT), LED270.2 (DIN)
unnamed: LED270.4 (DOUT), LED279.2 (DIN)
unnamed: LED271.2 (DIN), LED279.4 (DOUT)
unnamed: LED271.4 (DOUT), LED281.2 (DIN)
unnamed: LED272.2 (DIN), LED281.4 (DOUT)
unnamed: LED272.4 (DOUT), LED273.2 (DIN)
unnamed: LED273.4 (DOUT), LED274.2 (DIN)
unnamed: LED274.4 (DOUT), LED275.2 (DIN)
unnamed: LED275.4 (DOUT), R202.2

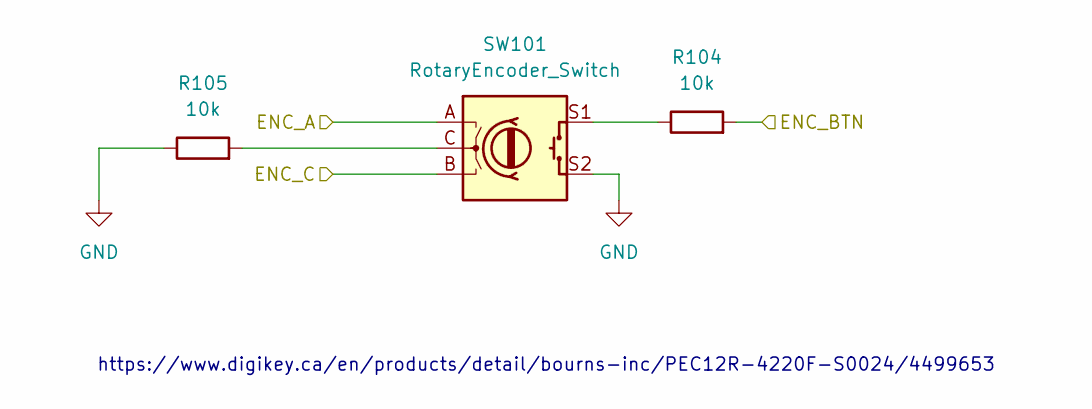
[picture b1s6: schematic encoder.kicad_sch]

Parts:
R104, R105: 10k; R_0603_1608Metric; JLC Part# C25804
SW101: RotaryEncoder_Switch; RotaryEncoder_Alps_EC11E-Switch_Vertical_H20mm_MountingHoles

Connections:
/Controller/GPIO27: SW101.A; also elsewhere on the board
/Controller/GPIO28: R104.2; also elsewhere on the board
/Controller/GPIO29: SW101.B; also elsewhere on the board
GND: R105.1, SW101.S2; also elsewhere on the board
unnamed: R104.1, SW101.S1
unnamed: R105.2, SW101.C

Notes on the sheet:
https://www.digikey.ca/en/products/detail/bourns-inc/PEC12R-4220F-S0024/4499653

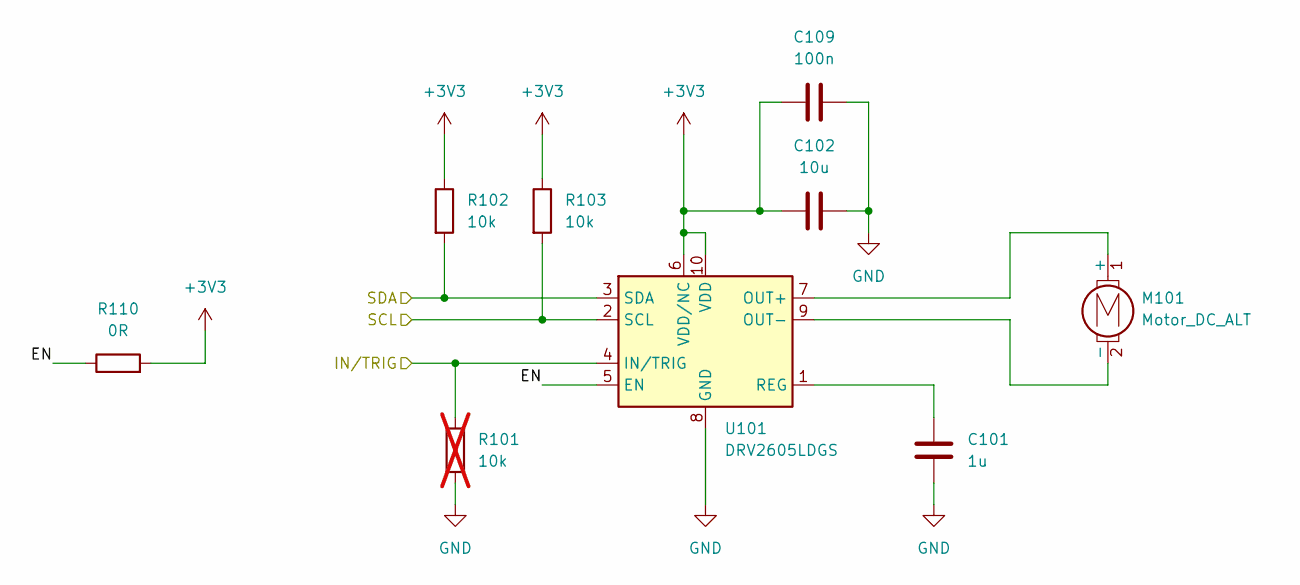
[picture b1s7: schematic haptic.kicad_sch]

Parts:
C101: 1u; C_0603_1608Metric; JLC Part# C15849
C102: 10u; C_0805_2012Metric; JLC Part# C15850
C109: 100n; C_0402_1005Metric; JLC Part# C307331
M101: Motor_DC_ALT; PinHeader_1x02_P2.54mm_Vertical
R101: 10k; R_0603_1608Metric; JLC Part# C25804; not fitted
R102, R103: 10k; R_0603_1608Metric; JLC Part# C25804
R110: 0R; R_0603_1608Metric; JLC Part# C21189
U101: DRV2605LDGS; TSSOP-10_3x3mm_P0.5mm

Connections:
+3V3: C102.1, C109.1, R102.1, R103.1, R110.2, U101.6 (VDD/NC), U101.10 (VDD); also elsewhere on the board
/Controller/GPIO32: R101.1, U101.4 (IN/TRIG); also elsewhere on the board
/Controller/GPIO34: R102.2, U101.3 (SDA); also elsewhere on the board
/Controller/GPIO35: R103.2, U101.2 (SCL); also elsewhere on the board
/Haptic/EN: R110.1, U101.5 (EN)
GND: C101.2, C102.2, C109.2, R101.2, U101.8 (GND); also elsewhere on the board
unnamed: M101.1 (+), U101.7 (OUT+)
unnamed: M101.2 (-), U101.9 (OUT-)
unnamed: C101.1, U101.1 (REG)
